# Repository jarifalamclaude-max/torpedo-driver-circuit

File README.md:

# Torpedo Driver v4

Two-channel solenoid driver for a 4S LiPo, controlled by an ESP32-C3 SuperMini.
The logic side (ESP32, `GNDL`) and the battery side (`GNDP`) are galvanically isolated: every signal crosses a 6.2 mm copper-free channel through a PC817 optocoupler, and the voltages are measured on the battery side by an ADS1115 that the ESP32 reads over opto-isolated I²C.

**Not yet built or tested on hardware.** Everything below is checked by DRC and by ngspice simulation only.

| Folder / file | Contents |
|---|---|
| `kicad/` | KiCad 7 PCB (`torpedo_driver_v4.kicad_pcb`), the scripts that build it (`build_v4.py`), route it (`route_v4.py` + `gridroute.py`) and brand it (`add_branding.py`), BOM (`bom_v4.csv`), DRC report (0 violations, 0 unconnected) |
| `kicad/simulation/` | ngspice simulation of the whole board taken from the PCB netlist: `run_all.py` (25 scenarios: normal, low battery, hot-plug, surges, shorts, open coils, wet board, boot), `i2c_timing.py` (opto I²C), `models.lib` (MOSFETs fitted to the datasheets, electromechanical solenoid) |
| `kicad-sim/` | Simulation-ready KiCad schematic for KiCad's built-in simulator |
| `firmware/` | ESP32-C3 Arduino sketch, and a PC test that runs it against a simulated ADS1115 |
| `gerber/` | Gerber and drill files for JLCPCB (2 layers, 100 × 88 mm) |
| `pcb-3d/` | 3D view of the board with the current paths and every part explained (`index.html`; serve the folder over http so the textures load) |
| `veroboard/` | Veroboard wiring plan generated from the PCB netlist, with a slider to spread the parts out, and the schematic (`torpedo_driver_v4_schematic.svg`) |
| `torpedo_driver_v4_*.zip` | The gerbers (ready for JLCPCB), the KiCad project, the simulation schematic and the firmware |

## What changed from v3

1. **Real isolation.** v3 joined the ESP32 ground to the battery minus, so the optos isolated nothing. v4 has two ground planes (`GNDL`, `GNDP`), a copper keep-out between them, and sensing moved to an ADS1115 on the battery side.
2. **Fuse that can break a LiPo short.** A 5 A fast ceramic 5×20 fuse (F2) in series with the RUEF300 PTC, whose interrupt rating is only 40 A.
3. **Q3 gate.** R14 1 kΩ (V<sub>gs</sub> −13.8 V at 16.8 V, −10.8 V at 13.2 V), D6 15 V clamp for surges, C11 100 nF so Q3 cannot turn on when the battery is plugged in.
4. **Opto drive.** 150 Ω LED resistors (11 mA), about 2× margin at the minimum PC817 CTR.
5. **Gate rail.** R9 680 Ω so Q1/Q2 still get 10.9 V at 13.2 V.
6. **Flyback diodes.** UF5408 instead of 1N5819: Schottky leakage made an open coil look connected.
7. **TVS.** P6KE22A instead of P6KE20A (standoff 18.8 V, above a full pack).
8. **Self-test.** R12 68 kΩ and four 200k/20k dividers: the firmware can tell healthy (VSW/VBAT 0.51), one coil open (0.60), fire MOSFET short (0.0002) and arm MOSFET short (1.00), and checks each coil separately.
9. **Firmware.** Fire pulses ended by a hardware timer (hard cap 500 ms), task watchdog, arm window, self-test before every arm, minimum battery voltage from the solenoid simulation.

## MOSFETs at the simulated operating point (16.8 V, 1.11 A per coil)

| Part | V<sub>gs</sub> | Datasheet R<sub>ds(on)</sub> max | Simulated drop | Power |
|---|---|---|---|---|
| Q1, Q2 IRLZ44N | 11.9 V (10.8 V at 13.2 V) | 22 mΩ at 10 V | 23.5 mV | 26 mW |
| Q3 IRF4905 | −13.8 V (−10.8 V at 13.2 V) | 20 mΩ at −10 V | 19.8 mV | 22 mW, 87 mW with both coils |

## Rules for using it

- **4S LiPo only** (no LiHV, no 5S). The firmware refuses to arm above 17.6 V.
- **Never join `GNDL` and `GNDP`.** The logic 5 V (J4 or USB) must not share a ground with the battery. If the Jetson runs from the same battery, feed the ESP32 through an isolated DC-DC.
- Unplug the battery when the AUV is stored.
- **Measure your solenoids** (resistance, inductance, stroke, plunger mass, spring force) and run `kicad/simulation/run_all.py` with your values. The defaults (vmin 14.4 V, 200 ms pulse) come from representative values, not from your coils.
- Run `CAL <volts>` once with a multimeter reading of the battery.

## GPIO map

GPIO1 fires SOL1, GPIO0 fires SOL2, GPIO10 arms, GPIO5 = I²C SCL out, GPIO6 = SDA out, GPIO7 = SDA read-back (all through optocouplers). GPIO8 (on-board LED) is on while armed.

## Rebuilding

With KiCad 7 and its Python (`KICAD7_FOOTPRINT_DIR` set to the KiCad footprint library):

```bash
cd kicad && python3 build_v4.py && python3 route_v4.py && python3 add_branding.py
```

Then `python3 simulation/run_all.py`, `python3 ../veroboard/make_vero_data.py` and `python3 ../pcb-3d/make_3d_data.py` refresh the simulation, the veroboard plan and the 3D view.

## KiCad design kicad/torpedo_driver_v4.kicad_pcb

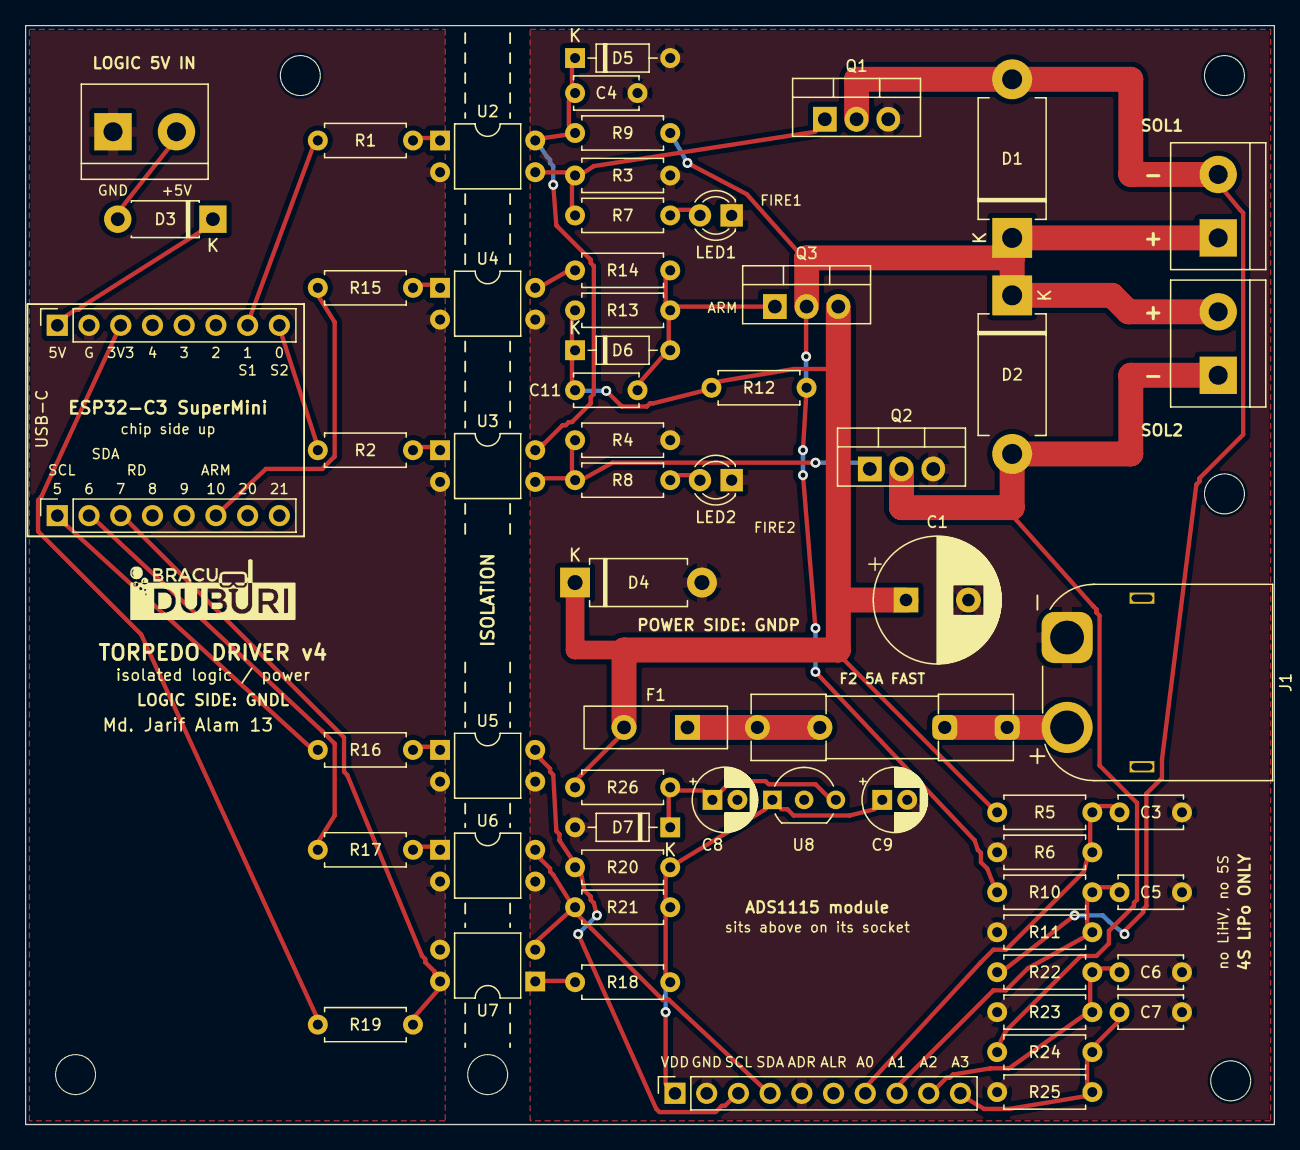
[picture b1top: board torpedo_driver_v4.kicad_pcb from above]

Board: 2 copper layers, 100.0 x 88.0 mm, 69 parts (0 on the bottom side), 38 nets.

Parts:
C1: 470uF 35V; CP_Radial_D10.0mm_P5.00mm
C3, C4, C5, C6, C7, C11: 100nF; C_Disc_D5.0mm_W2.5mm_P5.00mm
C8, C9: 10uF 35V; CP_Radial_D5.0mm_P2.00mm
D1, D2: UF5408; D_DO-201AD_P12.70mm_Horizontal
D3: 1N5819; D_DO-41_SOD81_P7.62mm_Horizontal
D4: P6KE22A; D_DO-15_P10.16mm_Horizontal
D5: 12V zener; D_DO-35_SOD27_P7.62mm_Horizontal
D6: 15V zener; D_DO-35_SOD27_P7.62mm_Horizontal
D7: 20V zener; D_DO-35_SOD27_P7.62mm_Horizontal
F1: RUEF300 PTC 3A 30V; PTC_Radial_P5.08mm_W11.5mm
F2: 5A fast 5x20 ceramic; Fuseholder_Clip-5x20mm_Littelfuse_111_Inline_P20.00x5.00mm_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
H1, H2, H3, H4, H5, H6: M3; MountingHole_3.2mm_M3
J1: XT60PW-M; AMASS_XT60PW-M_1x02_P7.20mm_Horizontal
J2: SOL1; TerminalBlock_bornier-2_P5.08mm
J3: SOL2; TerminalBlock_bornier-2_P5.08mm
J4: LOGIC 5V IN; TerminalBlock_bornier-2_P5.08mm
LED1, LED2: red 3mm; LED_D3.0mm
Q1, Q2: IRLZ44N; TO-220-3_Vertical
Q3: IRF4905; TO-220-3_Vertical
R1, R2, R15: 150; R_Axial_DIN0207_L6.3mm_D2.5mm_P7.62mm_Horizontal
R3, R4, R13: 4.7k; R_Axial_DIN0207_L6.3mm_D2.5mm_P7.62mm_Horizontal
R5, R10, R22, R24: 200k 1%; R_Axial_DIN0207_L6.3mm_D2.5mm_P7.62mm_Horizontal
R6, R11, R23, R25: 20k 1%; R_Axial_DIN0207_L6.3mm_D2.5mm_P7.62mm_Horizontal
R7, R8, R20, R21: 10k; R_Axial_DIN0207_L6.3mm_D2.5mm_P7.62mm_Horizontal
R9: 680; R_Axial_DIN0207_L6.3mm_D2.5mm_P7.62mm_Horizontal
R12: 68k 1%; R_Axial_DIN0207_L6.3mm_D2.5mm_P7.62mm_Horizontal
R14, R18, R26: 1k; R_Axial_DIN0207_L6.3mm_D2.5mm_P7.62mm_Horizontal
R16, R17: 220; R_Axial_DIN0207_L6.3mm_D2.5mm_P7.62mm_Horizontal
R19: 6.8k; R_Axial_DIN0207_L6.3mm_D2.5mm_P7.62mm_Horizontal
U1A: SuperMini 5V..IO0; PinSocket_1x08_P2.54mm_Vertical
U1B: SuperMini IO5..IO21; PinSocket_1x08_P2.54mm_Vertical
U2, U3, U4, U5, U6, U7: PC817; DIP-4_W7.62mm
U8: LP2950-3.3; TO-92_Inline_Wide
U9: ADS1115 module (GY-ADS1115); PinSocket_1x10_P2.54mm_Vertical

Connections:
3V3L: R19.1, U1A.3
3V3P: C9.1, R18.1, R20.2, R21.2, U8.1, U9.1
5V_IN: D3.2, J4.2
+5V: D3.1, U1A.1
ARM: R15.1, U1B.6
D1N: D1.2, J2.2, Q1.2, R22.1
D2N: D2.2, J3.1, Q2.2, R24.1
FIRE1: R1.1, U1A.7
FIRE2: R2.1, U1A.8
G1: Q1.1, R3.1, R7.1, U2.3
G2: Q2.1, R4.1, R8.1, U3.3
G3: C11.2, D6.2, Q3.1, R13.2, R14.2
G3D: R14.1, U4.4
GNDL: J4.1, U1A.2, U2.2, U3.2, U4.2, U5.2, U6.2, U7.3
GNDP: C1.2, C3.2, C4.2, C5.2, C6.2, C7.2, C8.2, C9.2, D4.2, D5.2, D7.2, J1.1, LED1.1, LED2.1, Q1.3, Q2.3, R3.2, R4.2, R6.1, R11.1, R23.1, R25.1, U4.3, U5.3, U6.3, U8.2, U9.2, U9.5
LED1A: LED1.2, R7.2
LED2A: LED2.2, R8.2
OL1: R1.2, U2.1
OL2: R2.2, U3.1
OL3: R15.2, U4.1
OSCL: R16.2, U5.1
OSDA: R17.2, U6.1
SBAT: C3.1, R5.2, R6.2, U9.7
SCL_P: R20.1, U5.4, U9.3
SCL_TX: R16.1, U1B.1
SD1: C6.1, R22.2, R23.2, U9.9
SD2: C7.1, R24.2, R25.2, U9.10
SDA_P: R21.1, U6.4, U7.2, U9.4
SDA_RX: R19.2, U1B.3, U7.4
SDA_TX: R17.1, U1B.2
SSW: C5.1, R10.2, R11.2, U9.8
U7A: R18.2, U7.1
VBAT: C1.1, C11.1, D4.1, D6.1, F1.2, Q3.3, R5.1, R12.1, R13.1, R26.1
VBAT_IN: F2.1, J1.2
VFUSE: F1.1, F2.2
VG: C4.1, D5.1, R9.1, U2.4, U3.4
VPRE: C8.1, D7.1, R26.2, U8.3
VSW: D1.1, D2.1, J2.1, J3.2, Q3.2, R9.2, R10.1, R12.2

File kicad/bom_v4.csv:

ref,value,footprint
C1,"470uF 35V",CP_Radial_D10.0mm_P5.00mm
C3,"100nF",C_Disc_D5.0mm_W2.5mm_P5.00mm
C4,"100nF",C_Disc_D5.0mm_W2.5mm_P5.00mm
C5,"100nF",C_Disc_D5.0mm_W2.5mm_P5.00mm
C6,"100nF",C_Disc_D5.0mm_W2.5mm_P5.00mm
C7,"100nF",C_Disc_D5.0mm_W2.5mm_P5.00mm
C8,"10uF 35V",CP_Radial_D5.0mm_P2.00mm
C9,"10uF 35V",CP_Radial_D5.0mm_P2.00mm
C11,"100nF",C_Disc_D5.0mm_W2.5mm_P5.00mm
D1,"UF5408",D_DO-201AD_P12.70mm_Horizontal
D2,"UF5408",D_DO-201AD_P12.70mm_Horizontal
D3,"1N5819",D_DO-41_SOD81_P7.62mm_Horizontal
D4,"P6KE22A",D_DO-15_P10.16mm_Horizontal
D5,"12V zener",D_DO-35_SOD27_P7.62mm_Horizontal
D6,"15V zener",D_DO-35_SOD27_P7.62mm_Horizontal
D7,"20V zener",D_DO-35_SOD27_P7.62mm_Horizontal
F1,"RUEF300 PTC 3A 30V",None
F2,"5A fast 5x20 ceramic",Fuseholder_Clip-5x20mm_Littelfuse_111_Inline_P20.00x5.00mm_D1.05mm_Horizontal
J1,"XT60PW-M",AMASS_XT60PW-M_1x02_P7.20mm_Horizontal
J2,"SOL1",TerminalBlock_bornier-2_P5.08mm
J3,"SOL2",TerminalBlock_bornier-2_P5.08mm
J4,"LOGIC 5V IN",TerminalBlock_bornier-2_P5.08mm
LED1,"red 3mm",LED_D3.0mm
LED2,"red 3mm",LED_D3.0mm
Q1,"IRLZ44N",TO-220-3_Vertical
Q2,"IRLZ44N",TO-220-3_Vertical
Q3,"IRF4905",TO-220-3_Vertical
R1,"150",R_Axial_DIN0207_L6.3mm_D2.5mm_P7.62mm_Horizontal
R2,"150",R_Axial_DIN0207_L6.3mm_D2.5mm_P7.62mm_Horizontal
R3,"4.7k",R_Axial_DIN0207_L6.3mm_D2.5mm_P7.62mm_Horizontal
R4,"4.7k",R_Axial_DIN0207_L6.3mm_D2.5mm_P7.62mm_Horizontal
R5,"200k 1%",R_Axial_DIN0207_L6.3mm_D2.5mm_P7.62mm_Horizontal
R6,"20k 1%",R_Axial_DIN0207_L6.3mm_D2.5mm_P7.62mm_Horizontal
R7,"10k",R_Axial_DIN0207_L6.3mm_D2.5mm_P7.62mm_Horizontal
R8,"10k",R_Axial_DIN0207_L6.3mm_D2.5mm_P7.62mm_Horizontal
R9,"680",R_Axial_DIN0207_L6.3mm_D2.5mm_P7.62mm_Horizontal
R10,"200k 1%",R_Axial_DIN0207_L6.3mm_D2.5mm_P7.62mm_Horizontal
R11,"20k 1%",R_Axial_DIN0207_L6.3mm_D2.5mm_P7.62mm_Horizontal
R12,"68k 1%",R_Axial_DIN0207_L6.3mm_D2.5mm_P7.62mm_Horizontal
R13,"4.7k",R_Axial_DIN0207_L6.3mm_D2.5mm_P7.62mm_Horizontal
R14,"1k",R_Axial_DIN0207_L6.3mm_D2.5mm_P7.62mm_Horizontal
R15,"150",R_Axial_DIN0207_L6.3mm_D2.5mm_P7.62mm_Horizontal
R16,"220",R_Axial_DIN0207_L6.3mm_D2.5mm_P7.62mm_Horizontal
R17,"220",R_Axial_DIN0207_L6.3mm_D2.5mm_P7.62mm_Horizontal
R18,"1k",R_Axial_DIN0207_L6.3mm_D2.5mm_P7.62mm_Horizontal
R19,"6.8k",R_Axial_DIN0207_L6.3mm_D2.5mm_P7.62mm_Horizontal
R20,"10k",R_Axial_DIN0207_L6.3mm_D2.5mm_P7.62mm_Horizontal
R21,"10k",R_Axial_DIN0207_L6.3mm_D2.5mm_P7.62mm_Horizontal
R22,"200k 1%",R_Axial_DIN0207_L6.3mm_D2.5mm_P7.62mm_Horizontal
R23,"20k 1%",R_Axial_DIN0207_L6.3mm_D2.5mm_P7.62mm_Horizontal
R24,"200k 1%",R_Axial_DIN0207_L6.3mm_D2.5mm_P7.62mm_Horizontal
R25,"20k 1%",R_Axial_DIN0207_L6.3mm_D2.5mm_P7.62mm_Horizontal
R26,"1k",R_Axial_DIN0207_L6.3mm_D2.5mm_P7.62mm_Horizontal
U1A,"SuperMini 5V..IO0",PinSocket_1x08_P2.54mm_Vertical
U1B,"SuperMini IO5..IO21",PinSocket_1x08_P2.54mm_Vertical
U2,"PC817",DIP-4_W7.62mm
U3,"PC817",DIP-4_W7.62mm
U4,"PC817",DIP-4_W7.62mm
U5,"PC817",DIP-4_W7.62mm
U6,"PC817",DIP-4_W7.62mm
U7,"PC817",DIP-4_W7.62mm
U8,"LP2950-3.3",TO-92_Inline_Wide
U9,"ADS1115 module (GY-ADS1115)",PinSocket_1x10_P2.54mm_Vertical

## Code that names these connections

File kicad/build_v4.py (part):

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place("U1B", *SOCK8, 2.54, 39.24, 90, "SuperMini IO5..IO21", {"1": "SCL_TX", "2": "SDA_TX", "3": "SDA_RX", "6": "ARM"})
place("J4", *TERM, 7.0, 8.5, 0, "LOGIC 5V IN", {"1": "GNDL", "2": "5V_IN"})
place("D3", *DO41, 15.0, 15.5, 180, "1N5819", {"1": "+5V", "2": "5V_IN"})
# opto rows (pin-1 y). Order along the barrier follows the power side: FIRE1, ARM, FIRE2, then the I2C link
YO = {"U2": 9.2, "U4": 21.0, "U3": 34.0, "U5": 58.0, "U6": 66.0, "U7": 76.54}
place("R1", *R, 23.4, YO["U2"], 0, "150", {"1": "FIRE1", "2": "OL1"})
place("R15", *R, 23.4, YO["U4"], 0, "150", {"1": "ARM", "2": "OL3"})
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# ============================ ISOLATION BARRIER ============================
# LED side (pins 1, 2) on the logic side, transistor side (pins 3, 4) on the power side.
place("U2", *DIP4, OPX, YO["U2"], 0, "PC817", {"1": "OL1", "2": "GNDL", "3": "G1", "4": "VG"})
place("U4", *DIP4, OPX, YO["U4"], 0, "PC817", {"1": "OL3", "2": "GNDL", "3": "GNDP", "4": "G3D"})
place("U3", *DIP4, OPX, YO["U3"], 0, "PC817", {"1": "OL2", "2": "GNDL", "3": "G2", "4": "VG"})
place("U5", *DIP4, OPX, YO["U5"], 0, "PC817", {"1": "OSCL", "2": "GNDL", "3": "GNDP", "4": "SCL_P"})
place("U6", *DIP4, OPX, YO["U6"], 0, "PC817", {"1": "OSDA", "2": "GNDL", "3": "GNDP", "4": "SDA_P"})
# U7 is turned round: its LED is driven from the power side, its transistor pulls the ESP input low
place("U7", *DIP4, OPX + 7.62, YO["U7"], 180, "PC817", {"1": "U7A", "2": "SDA_P", "3": "GNDL", "4": "SDA_RX"})

# ============================ POWER SIDE (GNDP) ============================
X1, X2 = 44.0, 51.62           # resistor/diode column next to the optos (pad 1, pad 2)
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        text(lab, 52.0 + 2.54 * i, 83.0, 0.8)
    # back side, on the empty logic area: GPIO map and the isolation rule
    text("GNDL and GNDP must stay separate", 16.0, 50.5, 0.8, layer=pcbnew.B_SilkS, bold=True)
    text("GPIO1>SOL1  GPIO0>SOL2  GPIO10=ARM", 16.0, 52.5, 0.8, layer=pcbnew.B_SilkS)
    text("GPIO5=SCL  GPIO6=SDA out  GPIO7=SDA in", 16.0, 54.2, 0.8, layer=pcbnew.B_SilkS)
    text("Torpedo driver v4", 16.0, 56.0, 0.8, layer=pcbnew.B_SilkS)

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
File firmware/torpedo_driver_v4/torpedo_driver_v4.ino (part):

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#include "esp_timer.h"

// ------------------------------------------------------------------ pins (see the back silkscreen)
const int PIN_FIRE1 = 1, PIN_FIRE2 = 0, PIN_ARM = 10;
const int PIN_SCL_TX = 5, PIN_SDA_TX = 6, PIN_SDA_RX = 7;
const int PIN_LED = 8;                       // SuperMini blue LED, active low: on while armed

// ------------------------------------------------------------------ limits and defaults
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const float DIVIDER = 11.0f;                  // 200k / 20k
const float ADC_LSB = 2.048f / 32768.0f;     // ADS1115 PGA +-2.048 V
const float VBAT_MAX = 17.6f;                // above a full 4S (and LiHV) means wrong battery
const float RATIO_IDLE_MIN = 0.30f, RATIO_IDLE_MAX = 0.80f;   // VSW/VBAT disarmed: 0.51 both coils, 0.60 one, 0.76 none
const float RATIO_ARMED_MIN = 0.95f;
const float COIL_OK = 0.85f, COIL_OPEN = 0.20f;               // DxN/VSW disarmed
const float FIRE_LOW = 0.10f;                                 // DxN/VBAT while the MOSFET is on

struct Settings { float gain = 1.0f; float vmin = 14.4f; uint32_t pulse_ms = 200; uint32_t arm_ms = 10000; } cfg;
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
// ------------------------------------------------------------------ outputs
void allOff() {
  digitalWrite(PIN_FIRE1, LOW); digitalWrite(PIN_FIRE2, LOW);
  digitalWrite(PIN_ARM, LOW); digitalWrite(PIN_LED, HIGH);
}
void fireOffCb(void*) { digitalWrite(PIN_FIRE1, LOW); digitalWrite(PIN_FIRE2, LOW); }
void armOffCb(void*) { allOff(); armed = false; }

void disarm(const char* why) {
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
// ------------------------------------------------------------------ opto-isolated I2C (bit-banged)
inline void wait(uint32_t us) { delayMicroseconds(us); }
inline void sclLow() { digitalWrite(PIN_SCL_TX, HIGH); }     // LED on -> line pulled low
inline void sclRelease() { digitalWrite(PIN_SCL_TX, LOW); }
inline void sdaLow() { digitalWrite(PIN_SDA_TX, HIGH); }
inline void sdaRelease() { digitalWrite(PIN_SDA_TX, LOW); }
inline bool sdaIsHigh() { return digitalRead(PIN_SDA_RX) == HIGH; }

void i2cStart() {            // SDA falls while SCL is high
  sdaRelease(); sclRelease(); wait(HALF_BIT_US);
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  if (armed) { msg = "already armed"; return true; }
  lastTest = selfTest();
  if (!lastTest.pass) { msg = "self-test failed: " + lastTest.why; lastFault = lastTest.why; return false; }
  digitalWrite(PIN_ARM, HIGH); delay(30);
  Reading r = readAll();
  if (!r.ok || r.vsw / r.vbat < RATIO_ARMED_MIN) { disarm("arm switch did not close (Q3/U4/R14)"); msg = "arm failed: " + lastFault; return false; }
  armed = true; armedAt = millis(); digitalWrite(PIN_LED, LOW);
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  if (haveFired && millis() - lastFire < MIN_GAP_MS) { msg = "too soon after the last pulse"; return false; }
  if (ms == 0) ms = cfg.pulse_ms;
  if (ms > MAX_PULSE_MS) ms = MAX_PULSE_MS;
  int pin = (ch == 1) ? PIN_FIRE1 : PIN_FIRE2;
  digitalWrite(pin, HIGH);
  esp_timer_start_once(fireTimer, (uint64_t)ms * 1000ULL);   // the timer, not this function, ends the pulse
  lastFire = millis(); haveFired = true;
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
// ------------------------------------------------------------------ setup / loop
void setup() {
  for (int p : {PIN_FIRE1, PIN_FIRE2, PIN_ARM, PIN_SCL_TX, PIN_SDA_TX}) { digitalWrite(p, LOW); pinMode(p, OUTPUT); digitalWrite(p, LOW); }
  pinMode(PIN_LED, OUTPUT); digitalWrite(PIN_LED, HIGH);
  pinMode(PIN_SDA_RX, INPUT);                    // 6.8k pull-up on the board (R19)
  Serial.begin(115200);
  loadSettings();
  esp_timer_create_args_t fa = {}; fa.callback = &fireOffCb; fa.name = "fire_off"; esp_timer_create(&fa, &fireTimer);
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    if (c == '\n' || c == '\r') { if (rx.length()) handle(rx); rx = ""; }
    else if (rx.length() < 64) rx += c;
  }
  if (!armed && digitalRead(PIN_ARM) == HIGH) allOff();            // arm timer fired: make sure everything is off
  if (armed && millis() - lastMon > 500) {                           // while armed, keep checking the arm switch
    lastMon = millis();
    float vb, vs;
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
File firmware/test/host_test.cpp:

// Behavioural ADS1115 behind the opto link: pin HIGH on GPIO5/6 pulls SCL/SDA low; GPIO7 reads SDA.
#include "Arduino.h"
#include <cmath>
SerialT Serial;
unsigned long g_us = 0;
static int pin[32];
static double node[4] = {16.8, 8.6, 8.6, 8.6};      // VBAT, VSW, D1N, D2N (volts at the board nodes)
static bool brokenQ1 = false;
static int armPinHigh() { return pin[10]; }
struct Slave { bool pull = false; int clk = 0; uint8_t sh = 0; int mode = 0; int byteNo = 0; bool rw = false; bool sel = false;
  uint8_t ptr = 0; uint16_t cfg = 0x8583; uint16_t conv = 0; uint8_t tx = 0; int txByte = 0; bool mack = false; } S;
static int starts = 0, stops = 0, nacks = 0;
static bool sclLine() { return !pin[5]; }
static bool sdaLine() { return !pin[6] && !S.pull; }
static void startConv() { int ch = ((S.cfg >> 12) & 7) - 4; double v = node[ch]; if (armPinHigh() && ch >= 1) v = node[0];
  if (ch == 2 && pin[1] && !brokenQ1) v = 0.02;
  if (ch == 3 && pin[0]) v = 0.02;
  S.conv = (uint16_t)(int16_t)std::lround(v / 11.0 / (2.048 / 32768.0)); }
static uint8_t txByteVal(int n) { uint16_t r = (S.ptr == 0) ? S.conv : S.cfg; return n == 0 ? r >> 8 : r & 0xFF; }
static void onStart() { starts++; S.mode = 1; S.clk = 0; S.sh = 0; S.byteNo = 0; S.pull = false; }
static void onStop() { stops++; S.mode = 0; S.pull = false; }
static void onRise(bool sda) { if (!S.mode) return; S.clk++;
  if (S.mode == 1 && S.clk <= 8) S.sh = (S.sh << 1) | sda;
  if (S.mode == 2 && S.clk == 9) S.mack = !sda; }
static uint16_t wbuf;
static void onFall() { if (!S.mode) return;
  if (S.mode == 1) {
    if (S.clk == 8) {
      if (S.byteNo == 0) { S.sel = ((S.sh >> 1) == 0x48); S.rw = S.sh & 1; if (!S.sel) nacks++; S.pull = S.sel; }
      else { if (S.byteNo == 1) S.ptr = S.sh; else if (S.byteNo == 2) wbuf = S.sh << 8; else if (S.byteNo == 3) { wbuf |= S.sh; if (S.ptr == 1) { S.cfg = wbuf; if (S.cfg & 0x8000) startConv(); } }
             S.pull = true; }
      S.byteNo++;
    } else if (S.clk == 9) { S.pull = false; S.clk = 0;
      if (S.byteNo == 1 && S.rw && S.sel) { S.mode = 2; S.txByte = 0; S.tx = txByteVal(0); S.pull = !(S.tx & 0x80); }
      if (!S.sel) S.mode = 0; }
  } else if (S.mode == 2) {
    if (S.clk < 8) S.pull = !((S.tx >> (7 - S.clk)) & 1);
    else if (S.clk == 8) S.pull = false;
    else if (S.clk == 9) { S.clk = 0; if (S.mack) { S.txByte++; S.tx = txByteVal(S.txByte); S.pull = !(S.tx & 0x80); } else { S.mode = 0; S.pull = false; } }
  } }
void digitalWrite(int p, int v) {
  bool scl0 = sclLine(), sda0 = sdaLine(); pin[p] = v; bool scl1 = sclLine(), sda1 = sdaLine();
  if (p == 5) { if (!scl0 && scl1) onRise(sda1); if (scl0 && !scl1) onFall(); }
  if (p == 6 && scl1) { if (sda0 && !sda1) onStart(); if (!sda0 && sda1) onStop(); } }
int digitalRead(int p) { return p == 7 ? (sdaLine() ? 1 : 0) : pin[p]; }
#include "../torpedo_driver_v4/torpedo_driver_v4.ino"
static void show(const char* name, TestResult t) { printf("%-22s pass=%d coil1=%d coil2=%d ok=%d vbat=%.2f vsw=%.2f d1n=%.2f d2n=%.2f  why=%s\n", name, t.pass, t.coil1, t.coil2,
  t.r.ok, t.r.vbat, t.r.vsw, t.r.d1n, t.r.d2n, t.why.c_str()); }
int main() {
  setup();
  show("idle 16.8 V", selfTest());
  node[1] = 16.8; node[2] = node[3] = 16.8; show("Q3 short", selfTest());
  node[1] = 0.01; node[2] = 0.0; node[3] = 0.01; show("Q1 short", selfTest());
  node[1] = 10.0; node[2] = 0.02; node[3] = 10.0; show("coil 1 open", selfTest());
  node[1] = 8.6; node[2] = 8.6; node[3] = 8.6; node[0] = 13.5; show("battery 13.5 V", selfTest());
  node[0] = 16.8; String m; bool ok = doArm(m); printf("arm: %d %s  armed=%d ARMpin=%d LED=%d\n", ok, m.c_str(), (int)armed, pin[10], pin[8]);
  ok = doFire(1, 0, m); printf("fire1: %d %s FIRE1pin=%d t=%lums\n", ok, m.c_str(), pin[1], millis());
  fireOffCb(nullptr);
  ok = doFire(2, 50, m); printf("fire2 again at once: %d %s\n", ok, m.c_str());
  g_us += 400000; ok = doFire(2, 900, m); printf("fire2 900ms request: %d %s\n", ok, m.c_str()); fireOffCb(nullptr);
  g_us += 400000; brokenQ1 = true; ok = doFire(1, 0, m); printf("fire1 with dead Q1: %d %s\n", ok, m.c_str()); fireOffCb(nullptr);
  ok = doFire(3, 0, m); printf("fire3: %d %s\n", ok, m.c_str());
  disarm(""); printf("disarm: armed=%d ARM=%d FIRE1=%d\n", (int)armed, pin[10], pin[1]);
  printf("bus: starts=%d stops=%d nacks=%d\n", starts, stops, nacks);
  return 0; }
